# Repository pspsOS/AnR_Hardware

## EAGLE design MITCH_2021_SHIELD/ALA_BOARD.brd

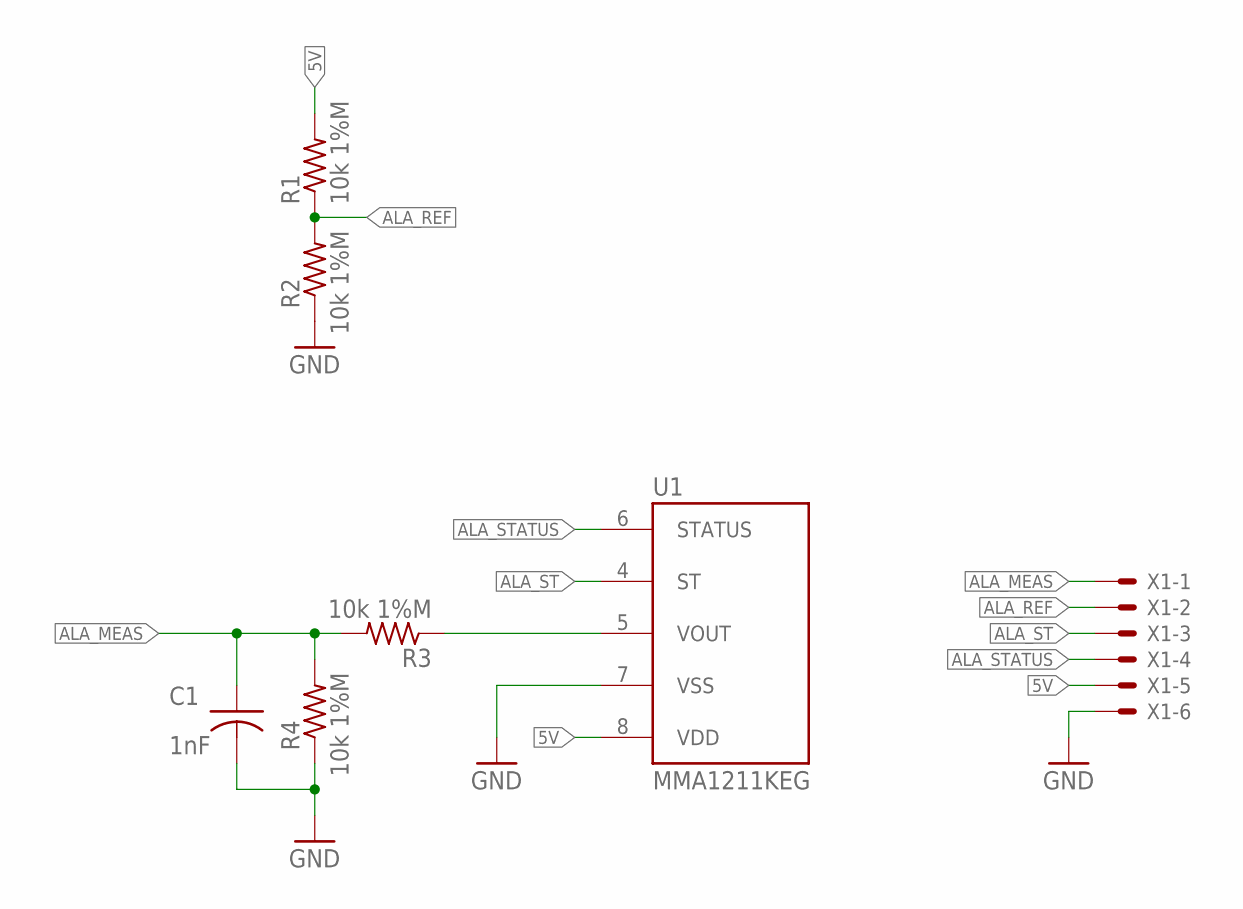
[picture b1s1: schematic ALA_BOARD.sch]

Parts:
C1: 1nF; C0805
R1, R2, R3, R4: 10k 1%M; R0805
U1: MMA1211KEG; SOIC127P1041X355-16N
X1: 22-23-2061

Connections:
5V: R1.2, U1.8 (VDD), X1.5
ALA_MEAS: C1.1, R3.2, R4.2, X1.1
ALA_REF: R1.1, R2.2, X1.2
ALA_ST: U1.4 (ST), X1.3
ALA_STATUS: U1.6 (STATUS), X1.4
GND: C1.2, R2.1, R4.1, U1.7 (VSS), X1.6
VOUT: R3.1, U1.5 (VOUT)

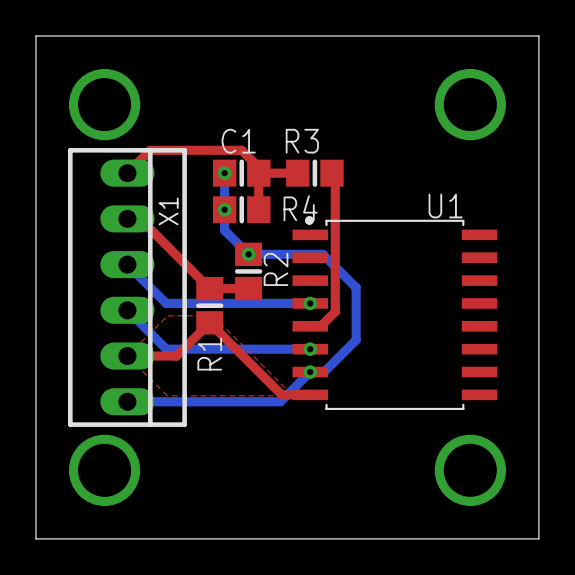
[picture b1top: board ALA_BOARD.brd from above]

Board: 2 copper layers, 27.9 x 27.9 mm, 7 parts (0 on the bottom side), 7 nets.

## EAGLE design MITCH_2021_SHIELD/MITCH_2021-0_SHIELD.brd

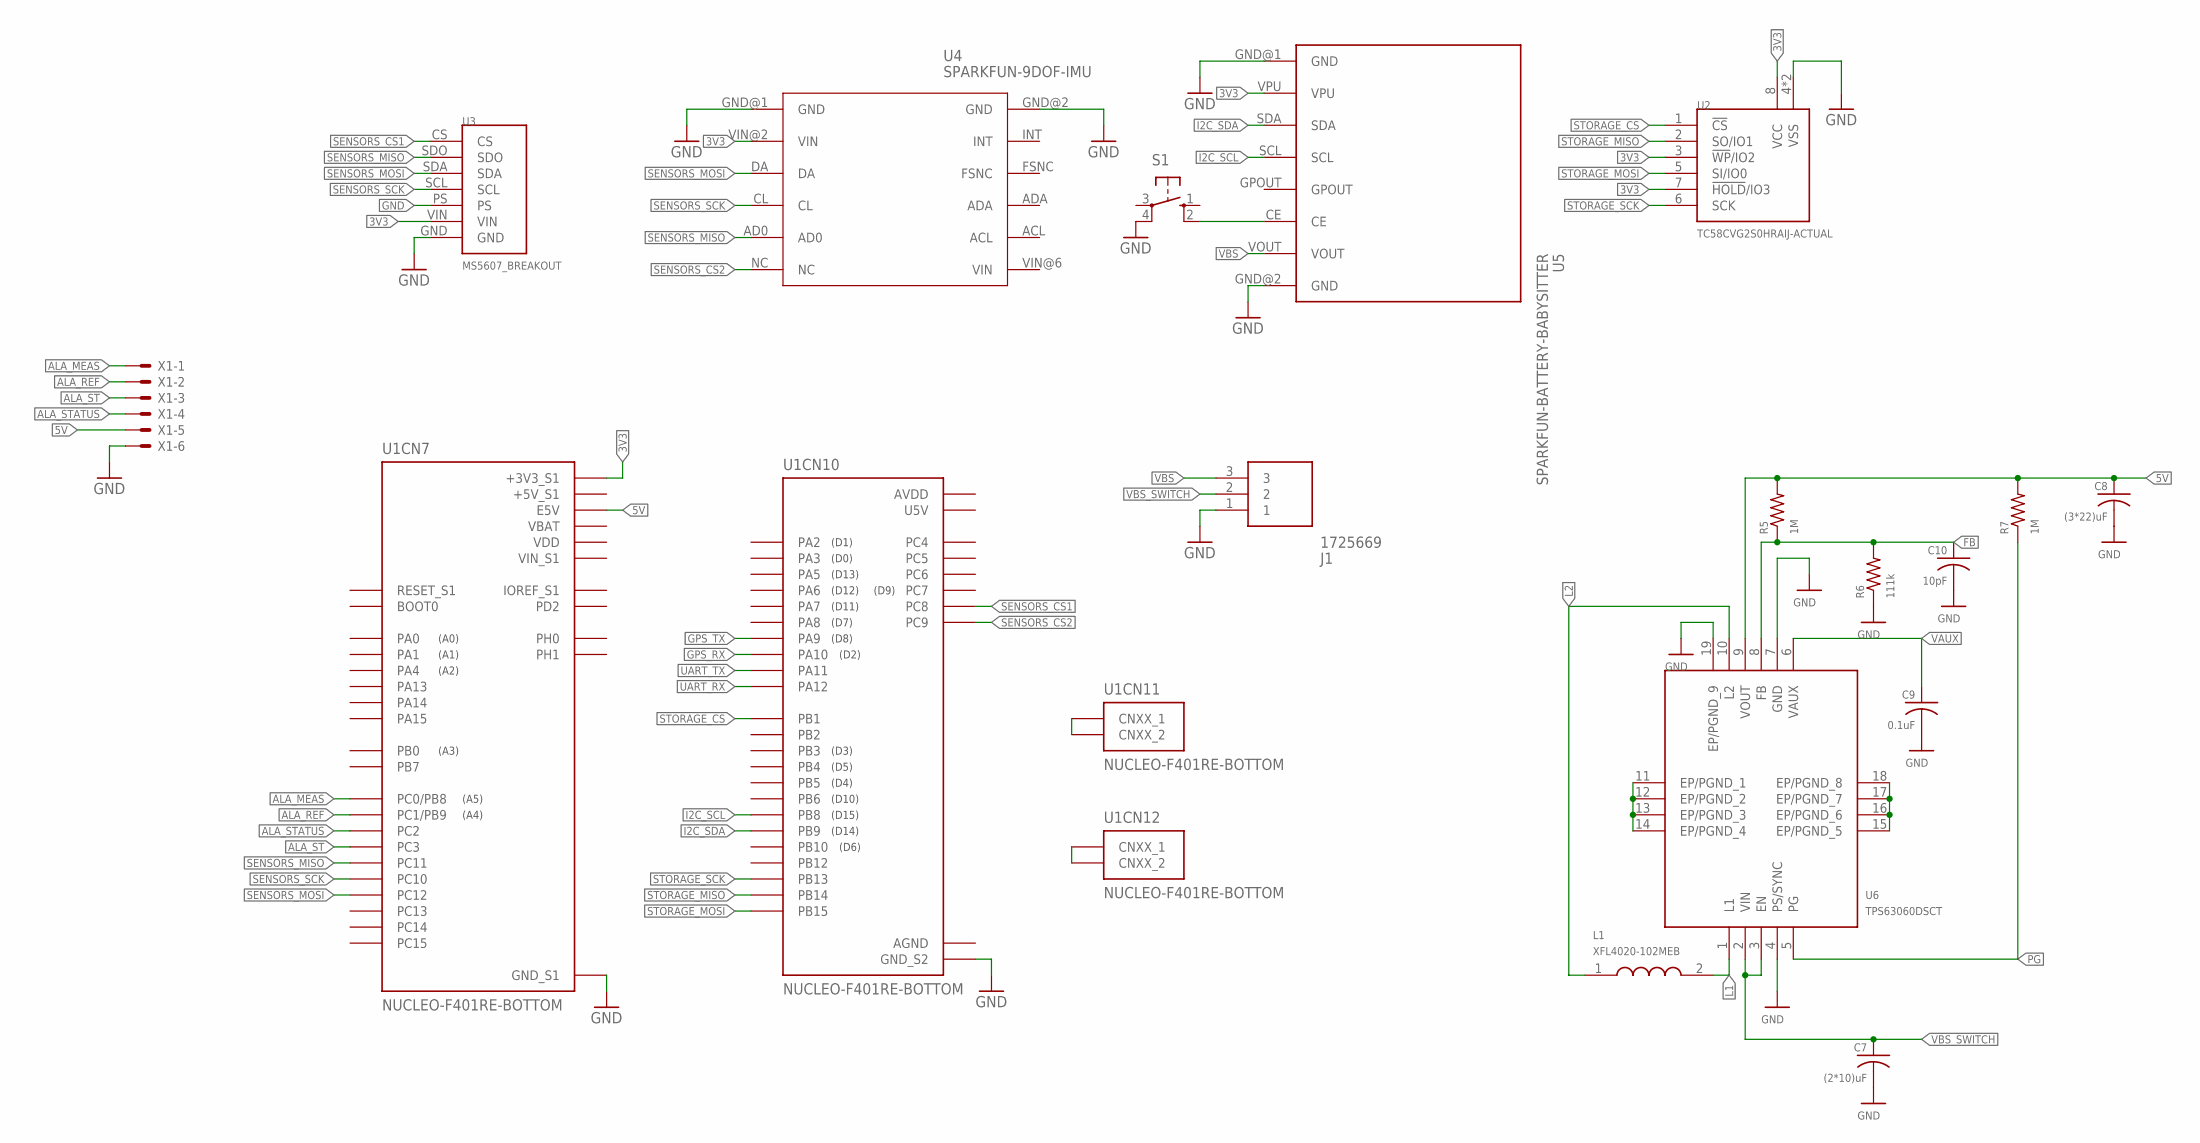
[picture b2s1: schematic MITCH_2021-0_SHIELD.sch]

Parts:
C7: (2*10)uF; C0805
C8: (3*22)uF; C0805
C9: 0.1uF; C0805
C10: 10pF; C0805
J1: 1725669
L1: XFL4020-102MEB; XFL4020102MEB
R5, R7: 1M; R0805
R6: 111k; R0805
S1: 10-XX; B3F-10XX
U1: NUCLEO-F401RE-BOTTOM; ST_NUCLEO-F401RE_BOTTOM
U2: TC58CVG2S0HRAIJ-ACTUAL; COMPUTER2_SON127P800X600X80-9T350X440N
U3: MS5607_BREAKOUT
U4: SPARKFUN-9DOF-IMU; SPARKFUN-9DOF-IMU1
U5: SPARKFUN-BATTERY-BABYSITTER
U6: TPS63060DSCT
X1: 22-23-2061

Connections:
3V3: U1.CN7_16 (+3V3_S1), U2.3 (!WP!/IO2), U2.7 (!HOLD!/IO3), U2.8 (VCC), U3.VIN, U4.VIN@2 (VIN), U5.VPU
5V: C8.1, R5.2, R7.2, U1.CN7_6 (E5V), U6.9 (VOUT), X1.5
+5V_S1: U1.CN7_18 (+5V_S1)
AGND: U1.CN10_32 (AGND)
ALA_MEAS: U1.CN7_38 (PC0/PB8), X1.1
ALA_REF: U1.CN7_36 (PC1/PB9), X1.2
ALA_ST: U1.CN7_37 (PC3), X1.3
ALA_STATUS: U1.CN7_35 (PC2), X1.4
AVDD: U1.CN10_7 (AVDD)
FB: C10.1, R5.1, R6.2, U6.8 (FB)
GND: C7.2, C8.2, C9.2, C10.2, J1.1, R6.1, S1.4 (P1), U1.CN7_8 (GND_S1), U1.CN7_19 (GND_S1), U1.CN7_20 (GND_S1), U1.CN7_22 (GND_S1), U1.CN10_9 (GND_S2), U1.CN10_20 (GND_S2), U2.4 (VSS), U2.9 (VSS), U3.GND, U3.PS, U4.GND@1 (GND), U4.GND@2 (GND), U5.GND@1 (GND), U5.GND@2 (GND), U6.4 (PS/SYNC), U6.7 (GND), U6.11 (EP/PGND_1), U6.12 (EP/PGND_2), U6.13 (EP/PGND_3), U6.14 (EP/PGND_4), U6.15 (EP/PGND_5), U6.16 (EP/PGND_6), U6.17 (EP/PGND_7), U6.18 (EP/PGND_8), U6.19 (EP/PGND_9), X1.6
GPS_RX: U1.CN10_33 (PA10)
GPS_TX: U1.CN10_21 (PA9)
I2C_SCL: U1.CN10_3 (PB8), U5.SCL
I2C_SDA: U1.CN10_5 (PB9), U5.SDA
L1: L1.2, U6.1 (L1)
L2: L1.1, U6.10 (L2)
unnamed: U1.CN12_1 (CNXX_1), U1.CN12_2 (CNXX_2)
unnamed: U1.CN11_1 (CNXX_1), U1.CN11_2 (CNXX_2)
unnamed: S1.2 (S1), U5.CE
PG: R7.1, U6.5 (PG)
SENSORS_CS1: U1.CN10_2 (PC8), U3.CS
SENSORS_CS2: U1.CN10_1 (PC9), U4.NC
SENSORS_MISO: U1.CN7_2 (PC11), U3.SDO, U4.AD0
SENSORS_MOSI: U1.CN7_3 (PC12), U3.SDA, U4.DA
SENSORS_SCK: U1.CN7_1 (PC10), U3.SCL, U4.CL
STORAGE_CS: U1.CN10_24 (PB1), U2.1 (!CS!)
STORAGE_MISO: U1.CN10_28 (PB14), U2.2 (SO/IO1)
STORAGE_MOSI: U1.CN10_26 (PB15), U2.5 (SI/IO0)
STORAGE_SCK: U1.CN10_30 (PB13), U2.6 (SCK)
U5V: U1.CN10_8 (U5V)
UART_RX: U1.CN10_12 (PA12)
UART_TX: U1.CN10_14 (PA11)
VAUX: C9.1, U6.6 (VAUX)
VBAT: U1.CN7_33 (VBAT)
VBS: J1.3, U5.VOUT
VBS_SWITCH: C7.1, J1.2, U6.2 (VIN), U6.3 (EN)
VDD: U1.CN7_5 (VDD)
VIN_S1: U1.CN7_24 (VIN_S1)

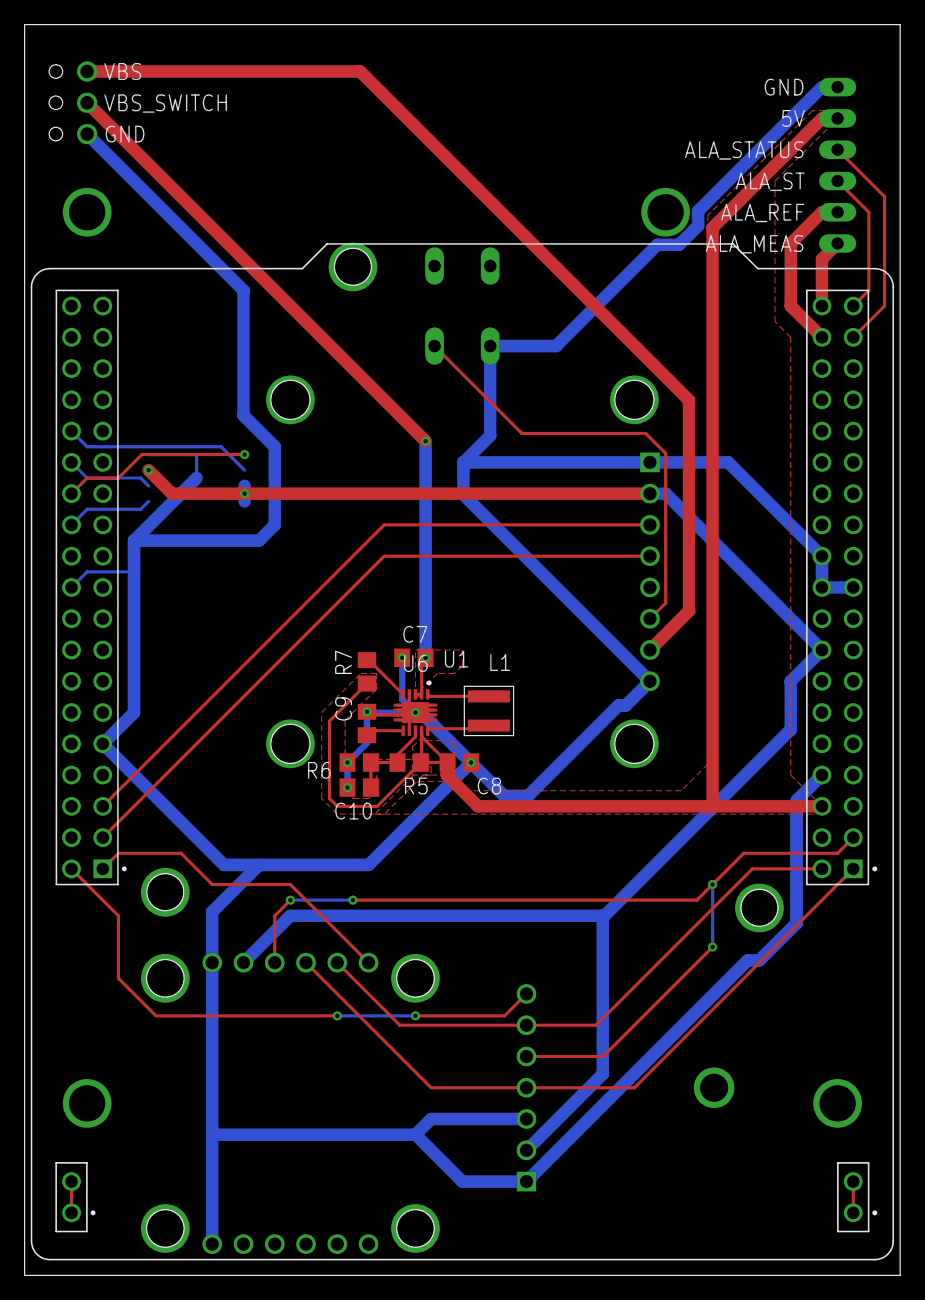
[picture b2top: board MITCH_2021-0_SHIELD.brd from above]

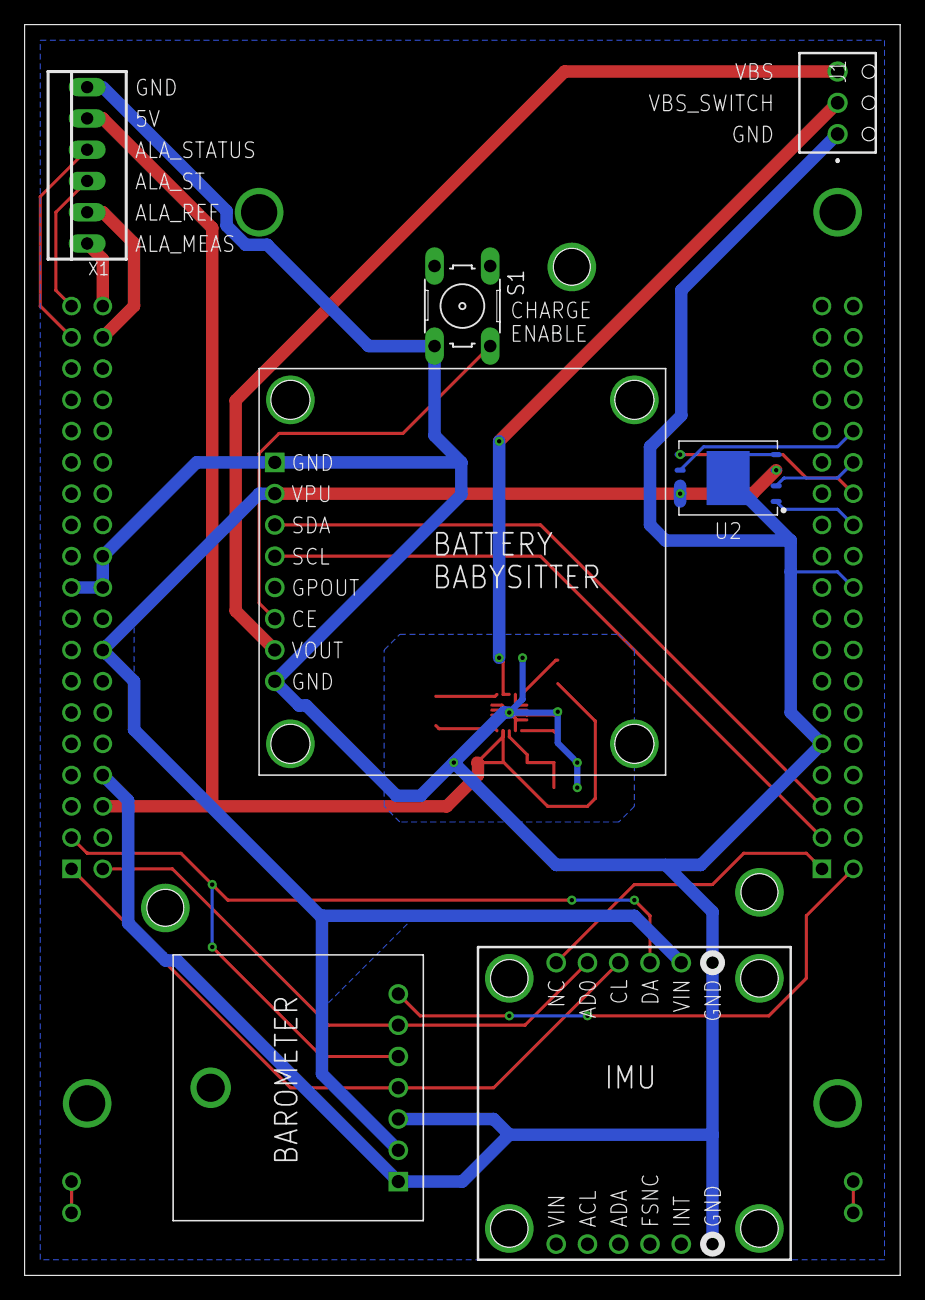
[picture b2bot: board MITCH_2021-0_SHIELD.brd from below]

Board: 2 copper layers, 71.1 x 101.6 mm, 17 parts (7 on the bottom side), 28 nets.

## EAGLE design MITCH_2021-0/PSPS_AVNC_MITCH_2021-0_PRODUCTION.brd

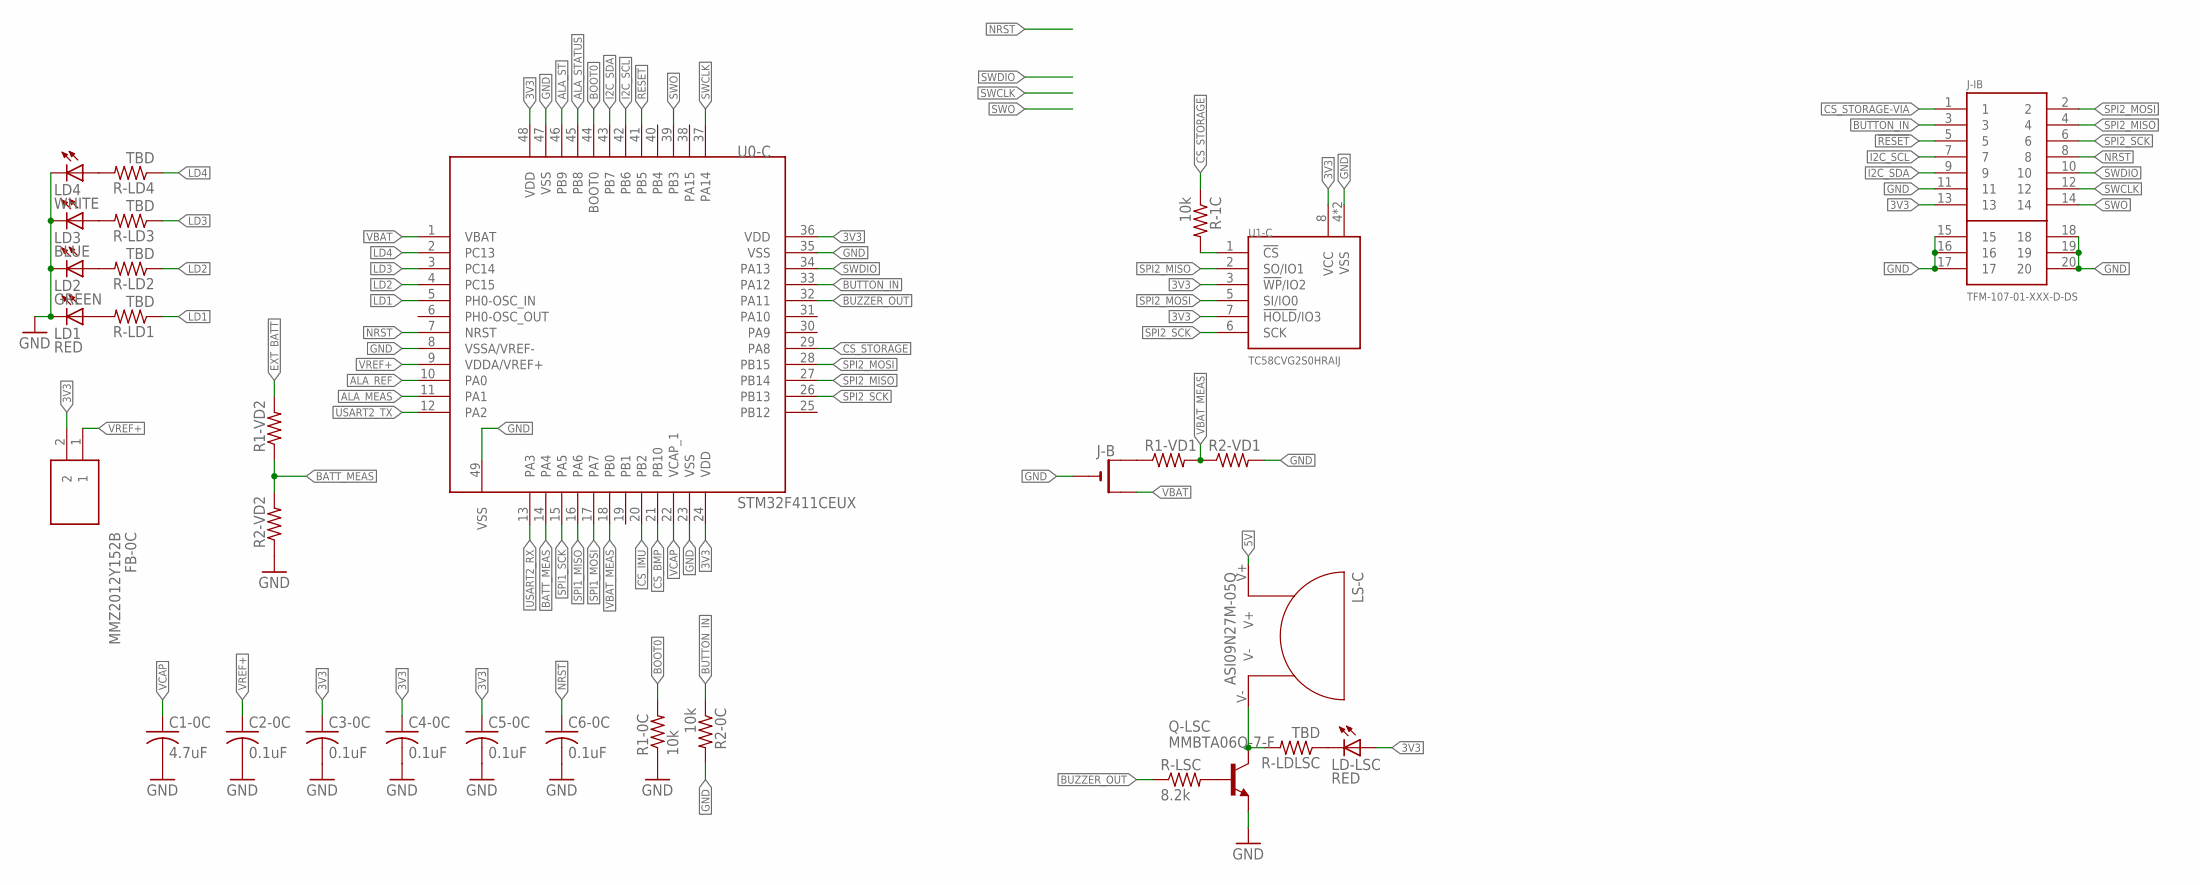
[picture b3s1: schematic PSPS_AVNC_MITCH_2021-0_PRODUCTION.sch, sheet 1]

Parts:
C1-0C: 4.7uF; C0805
C2-0C, C3-0C, C4-0C, C5-0C, C6-0C: 0.1uF; C0805
FB-0C: MMZ2012Y152B; BEADC2012X105N
J-B: CR1220SMT; CR1220-SMD
J-IB: TFM-107-01-XXX-D-DS
LD1: RED; CHIPLED_0805
LD2: GREEN; CHIPLED_0805
LD3: BLUE; CHIPLED_0805
LD4: WHITE; CHIPLED_0805
LD-LSC: RED; CHIPLED_0805
LS-C: ASI09N27M-05Q
Q-LSC: MMBTA06Q-7-F; SOT23
R1-0C, R2-0C: 10k; R0805
R1-VD1, R1-VD2, R2-VD1, R2-VD2: R-US_R0805; R0805
R-1C: 10k; R0805
R-LD1, R-LD2, R-LD3, R-LD4: TBD; R0805
R-LDLSC: TBD; R0805
R-LSC: 8.2k; R0805
U0-C: STM32F411CEUX; QFN50P700X700X50-49T560N
U1-C: TC58CVG2S0HRAIJ; SON127P800X600X80-9T350X440N

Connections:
3V3: C3-0C.1, C4-0C.1, C5-0C.1, FB-0C.2, J-IB.13, LD-LSC.A, U0-C.24 (VDD), U0-C.36 (VDD), U0-C.48 (VDD), U1-C.3 (!WP!/IO2), U1-C.7 (!HOLD!/IO3), U1-C.8 (VCC); also elsewhere on the board
5V: LS-C.V+; also elsewhere on the board
!RESET!: J-IB.5, U0-C.41 (PB5)
ALA_MEAS: U0-C.11 (PA1); also elsewhere on the board
ALA_REF: U0-C.10 (PA0); also elsewhere on the board
ALA_ST: U0-C.46 (PB9); also elsewhere on the board
ALA_STATUS: U0-C.45 (PB8); also elsewhere on the board
BATT_MEAS: R1-VD2.1, R2-VD2.2, U0-C.14 (PA4)
BOOT0: R1-0C.2, U0-C.44 (BOOT0)
BUTTON_IN: J-IB.3, R2-0C.1, U0-C.33 (PA12)
BUZZER_OUT: R-LSC.1, U0-C.32 (PA11)
CS_BMP: U0-C.21 (PB10); also elsewhere on the board
CS_IMU: U0-C.20 (PB2); also elsewhere on the board
CS_STORAGE: R-1C.1, U0-C.29 (PA8)
CS_STORAGE-VIA: J-IB.1, R-1C.2, U1-C.1 (!CS!)
EXT_BATT: R1-VD2.2
GND: C1-0C.2, C2-0C.2, C3-0C.2, C4-0C.2, C5-0C.2, C6-0C.2, J-B.-, J-IB.11, J-IB.15, J-IB.16, J-IB.17, J-IB.18, J-IB.19, J-IB.20, LD1.C, LD2.C, LD3.C, LD4.C, Q-LSC.3 (E), R1-0C.1, R2-0C.2, R2-VD1.2, R2-VD2.1, U0-C.8 (VSSA/VREF-), U0-C.23 (VSS), U0-C.35 (VSS), U0-C.47 (VSS), U0-C.49 (VSS), U1-C.4 (VSS), U1-C.9 (VSS); also elsewhere on the board
I2C_SCL: J-IB.7, U0-C.42 (PB6)
I2C_SDA: J-IB.9, U0-C.43 (PB7)
LD1: R-LD1.1, U0-C.5 (PH0-OSC_IN)
LD2: R-LD2.1, U0-C.4 (PC15)
LD3: R-LD3.1, U0-C.3 (PC14)
LD4: R-LD4.1, U0-C.2 (PC13)
unnamed: Q-LSC.1 (B), R-LSC.2
unnamed: LD1.A, R-LD1.2
unnamed: LD2.A, R-LD2.2
unnamed: LD3.A, R-LD3.2
unnamed: LD4.A, R-LD4.2
unnamed: J-B.+$1 (+), R1-VD1.1
unnamed: LS-C.V-, Q-LSC.2 (C), R-LDLSC.2
unnamed: LD-LSC.C, R-LDLSC.1
NRST: C6-0C.1, J-IB.8, U0-C.7 (NRST)
SPI1_MISO: U0-C.16 (PA6); also elsewhere on the board
SPI1_MOSI: U0-C.17 (PA7); also elsewhere on the board
SPI1_SCK: U0-C.15 (PA5); also elsewhere on the board
SPI2_MISO: J-IB.4, U0-C.27 (PB14), U1-C.2 (SO/IO1)
SPI2_MOSI: J-IB.2, U0-C.28 (PB15), U1-C.5 (SI/IO0)
SPI2_SCK: J-IB.6, U0-C.26 (PB13), U1-C.6 (SCK)
SWCLK: J-IB.12, U0-C.37 (PA14)
SWDIO: J-IB.10, U0-C.34 (PA13)
SWO: J-IB.14, U0-C.39 (PB3)
USART2_RX: U0-C.13 (PA3); also elsewhere on the board
USART2_TX: U0-C.12 (PA2); also elsewhere on the board
VBAT: J-B.+$2 (+1), U0-C.1 (VBAT); also elsewhere on the board
VBAT_MEAS: R1-VD1.2, R2-VD1.1, U0-C.18 (PB0)
VCAP: C1-0C.1, U0-C.22 (VCAP_1)
VREF+: C2-0C.1, FB-0C.1, U0-C.9 (VDDA/VREF+)

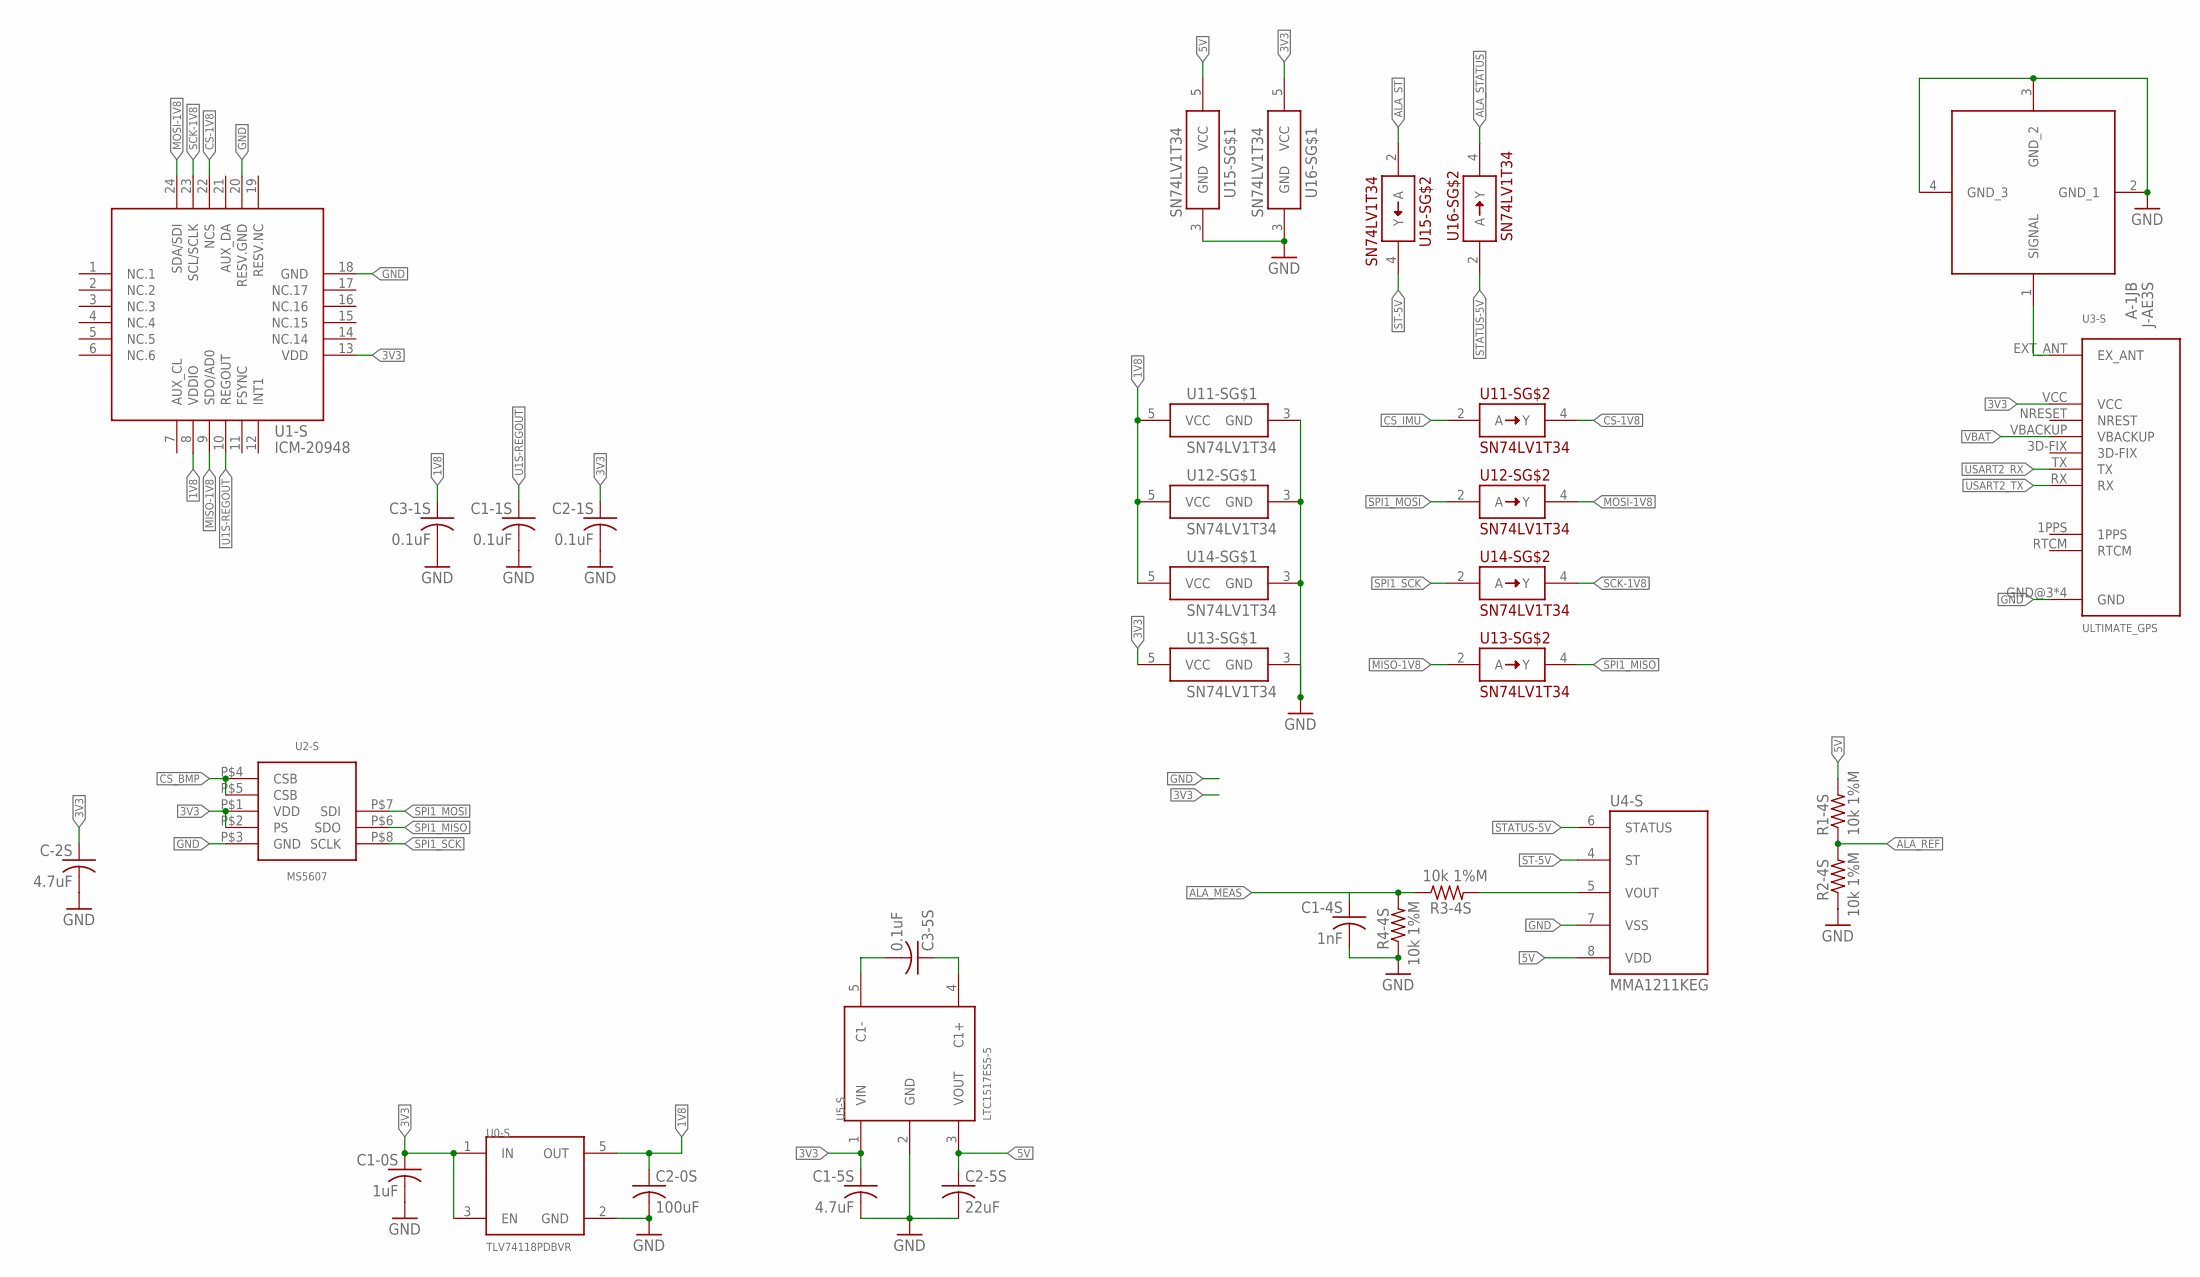
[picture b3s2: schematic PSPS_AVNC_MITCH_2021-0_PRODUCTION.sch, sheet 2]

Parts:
C1-0S: 1uF; C0805
C1-1S, C2-1S, C3-1S, C3-5S: 0.1uF; C0805
C1-4S: 1nF; C0805
C1-5S: 4.7uF; C0805
C2-0S: 100uF; C0805
C2-5S: 22uF; C0805
C-2S: 4.7uF; C0805
J-AE3S: A-1JB; A1JB
R1-4S, R2-4S, R3-4S, R4-4S: 10k 1%M; R0805
U0-S: TLV74118PDBVR; SOT95P280X145-5N
U1-S: ICM-20948; QFN40P300X300X105-25T159X175
U2-S: MS5607
U3-S: ULTIMATE_GPS; FGPMMOPA6H
U4-S: MMA1211KEG; SOIC127P1041X355-16N
U5-S: LTC1517ES5-5; SOT95P280X145-5N
U11-S, U12-S, U13-S, U14-S, U15-S, U16-S: SN74LV1T34; SOT65P210X110-5

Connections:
1V8: C2-0S.1, C3-1S.1, U0-S.5 (OUT), U1-S.8 (VDDIO), U11-S.5 (VCC), U12-S.5 (VCC), U14-S.5 (VCC)
3V3: C1-0S.1, C1-5S.1, C2-1S.1, C-2S.1, U0-S.1 (IN), U0-S.3 (EN), U1-S.13 (VDD), U2-S.P$1 (VDD), U2-S.P$2 (PS), U3-S.VCC, U5-S.1 (VIN), U13-S.5 (VCC), U16-S.5 (VCC); also elsewhere on the board
5V: C2-5S.1, R1-4S.2, U4-S.8 (VDD), U5-S.3 (VOUT), U15-S.5 (VCC); also elsewhere on the board
ALA_MEAS: C1-4S.1, R3-4S.1, R4-4S.2; also elsewhere on the board
ALA_REF: R1-4S.1, R2-4S.2; also elsewhere on the board
ALA_ST: U15-S.2 (A); also elsewhere on the board
ALA_STATUS: U16-S.4 (Y); also elsewhere on the board
CS-1V8: U1-S.22 (NCS), U11-S.4 (Y)
CS_BMP: U2-S.P$4 (CSB), U2-S.P$5 (CSB); also elsewhere on the board
CS_IMU: U11-S.2 (A); also elsewhere on the board
GND: C1-0S.2, C1-1S.2, C1-4S.2, C1-5S.2, C2-0S.2, C2-1S.2, C2-5S.2, C3-1S.2, C-2S.2, J-AE3S.2 (GND_1), J-AE3S.3 (GND_2), J-AE3S.4 (GND_3), R2-4S.1, R4-4S.1, U0-S.2 (GND), U1-S.18 (GND), U1-S.20 (RESV.GND), U2-S.P$3 (GND), U3-S.GND@3 (GND), U3-S.GND@8 (GND), U3-S.GND@12 (GND), U3-S.GND@19 (GND), U4-S.7 (VSS), U5-S.2 (GND), U11-S.3 (GND), U12-S.3 (GND), U13-S.3 (GND), U14-S.3 (GND), U15-S.3 (GND), U16-S.3 (GND); also elsewhere on the board
MISO-1V8: U1-S.9 (SDO/AD0), U13-S.2 (A)
MOSI-1V8: U1-S.24 (SDA/SDI), U12-S.4 (Y)
unnamed: C3-5S.1, U5-S.4 (C1+)
unnamed: C3-5S.2, U5-S.5 (C1-)
unnamed: J-AE3S.1 (SIGNAL), U3-S.EXT_ANT (EX_ANT)
unnamed: R3-4S.2, U4-S.5 (VOUT)
SCK-1V8: U1-S.23 (SCL/SCLK), U14-S.4 (Y)
SPI1_MISO: U2-S.P$6 (SDO), U13-S.4 (Y); also elsewhere on the board
SPI1_MOSI: U2-S.P$7 (SDI), U12-S.2 (A); also elsewhere on the board
SPI1_SCK: U2-S.P$8 (SCLK), U14-S.2 (A); also elsewhere on the board
ST-5V: U4-S.4 (ST), U15-S.4 (Y)
STATUS-5V: U4-S.6 (STATUS), U16-S.2 (A)
U1S-REGOUT: C1-1S.1, U1-S.10 (REGOUT)
USART2_RX: U3-S.TX; also elsewhere on the board
USART2_TX: U3-S.RX; also elsewhere on the board
VBAT: U3-S.VBACKUP; also elsewhere on the board

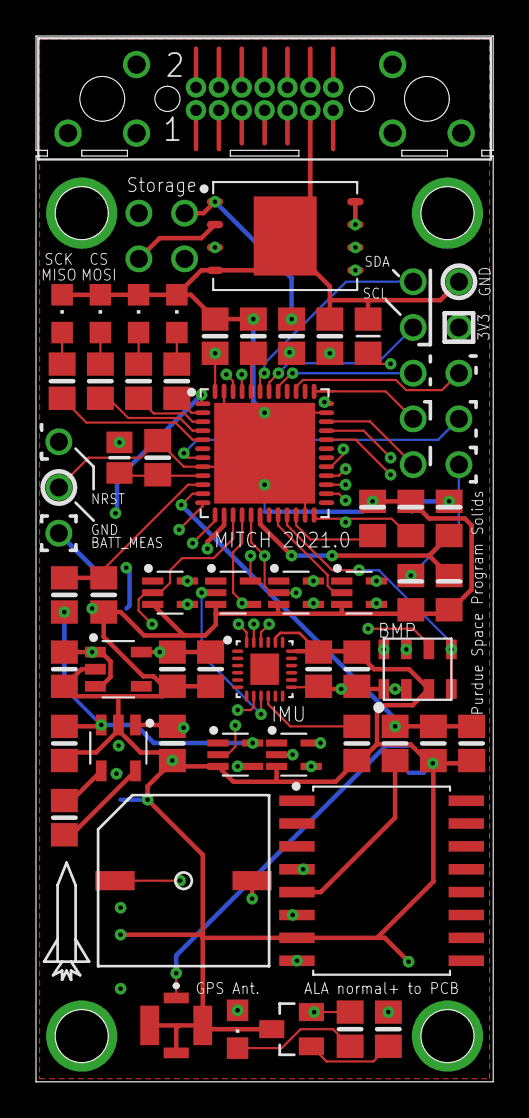
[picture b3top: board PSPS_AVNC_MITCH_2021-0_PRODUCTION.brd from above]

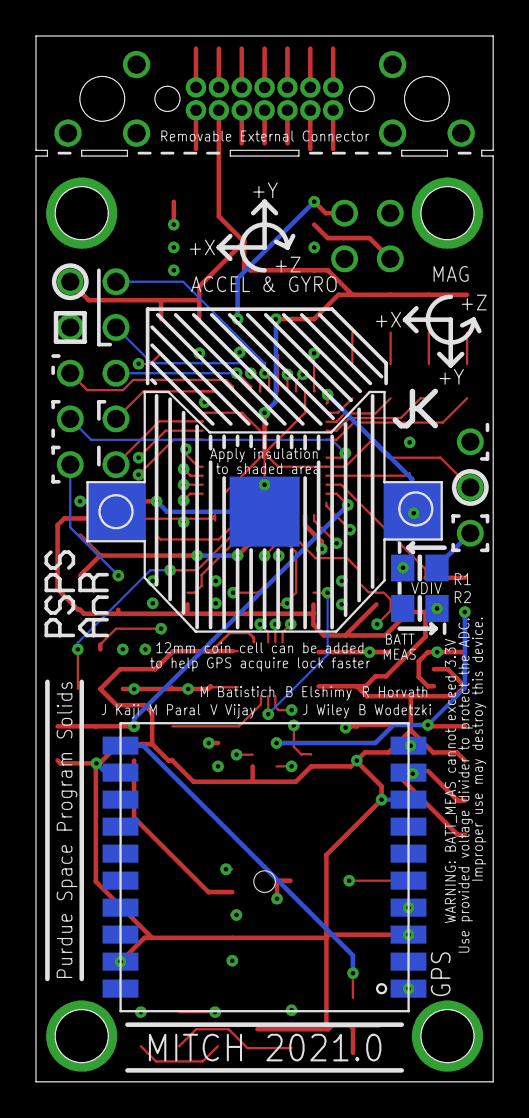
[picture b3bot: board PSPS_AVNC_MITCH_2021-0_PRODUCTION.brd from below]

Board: 4 copper layers, 25.4 x 58.1 mm, 58 parts (4 on the bottom side), 58 nets.

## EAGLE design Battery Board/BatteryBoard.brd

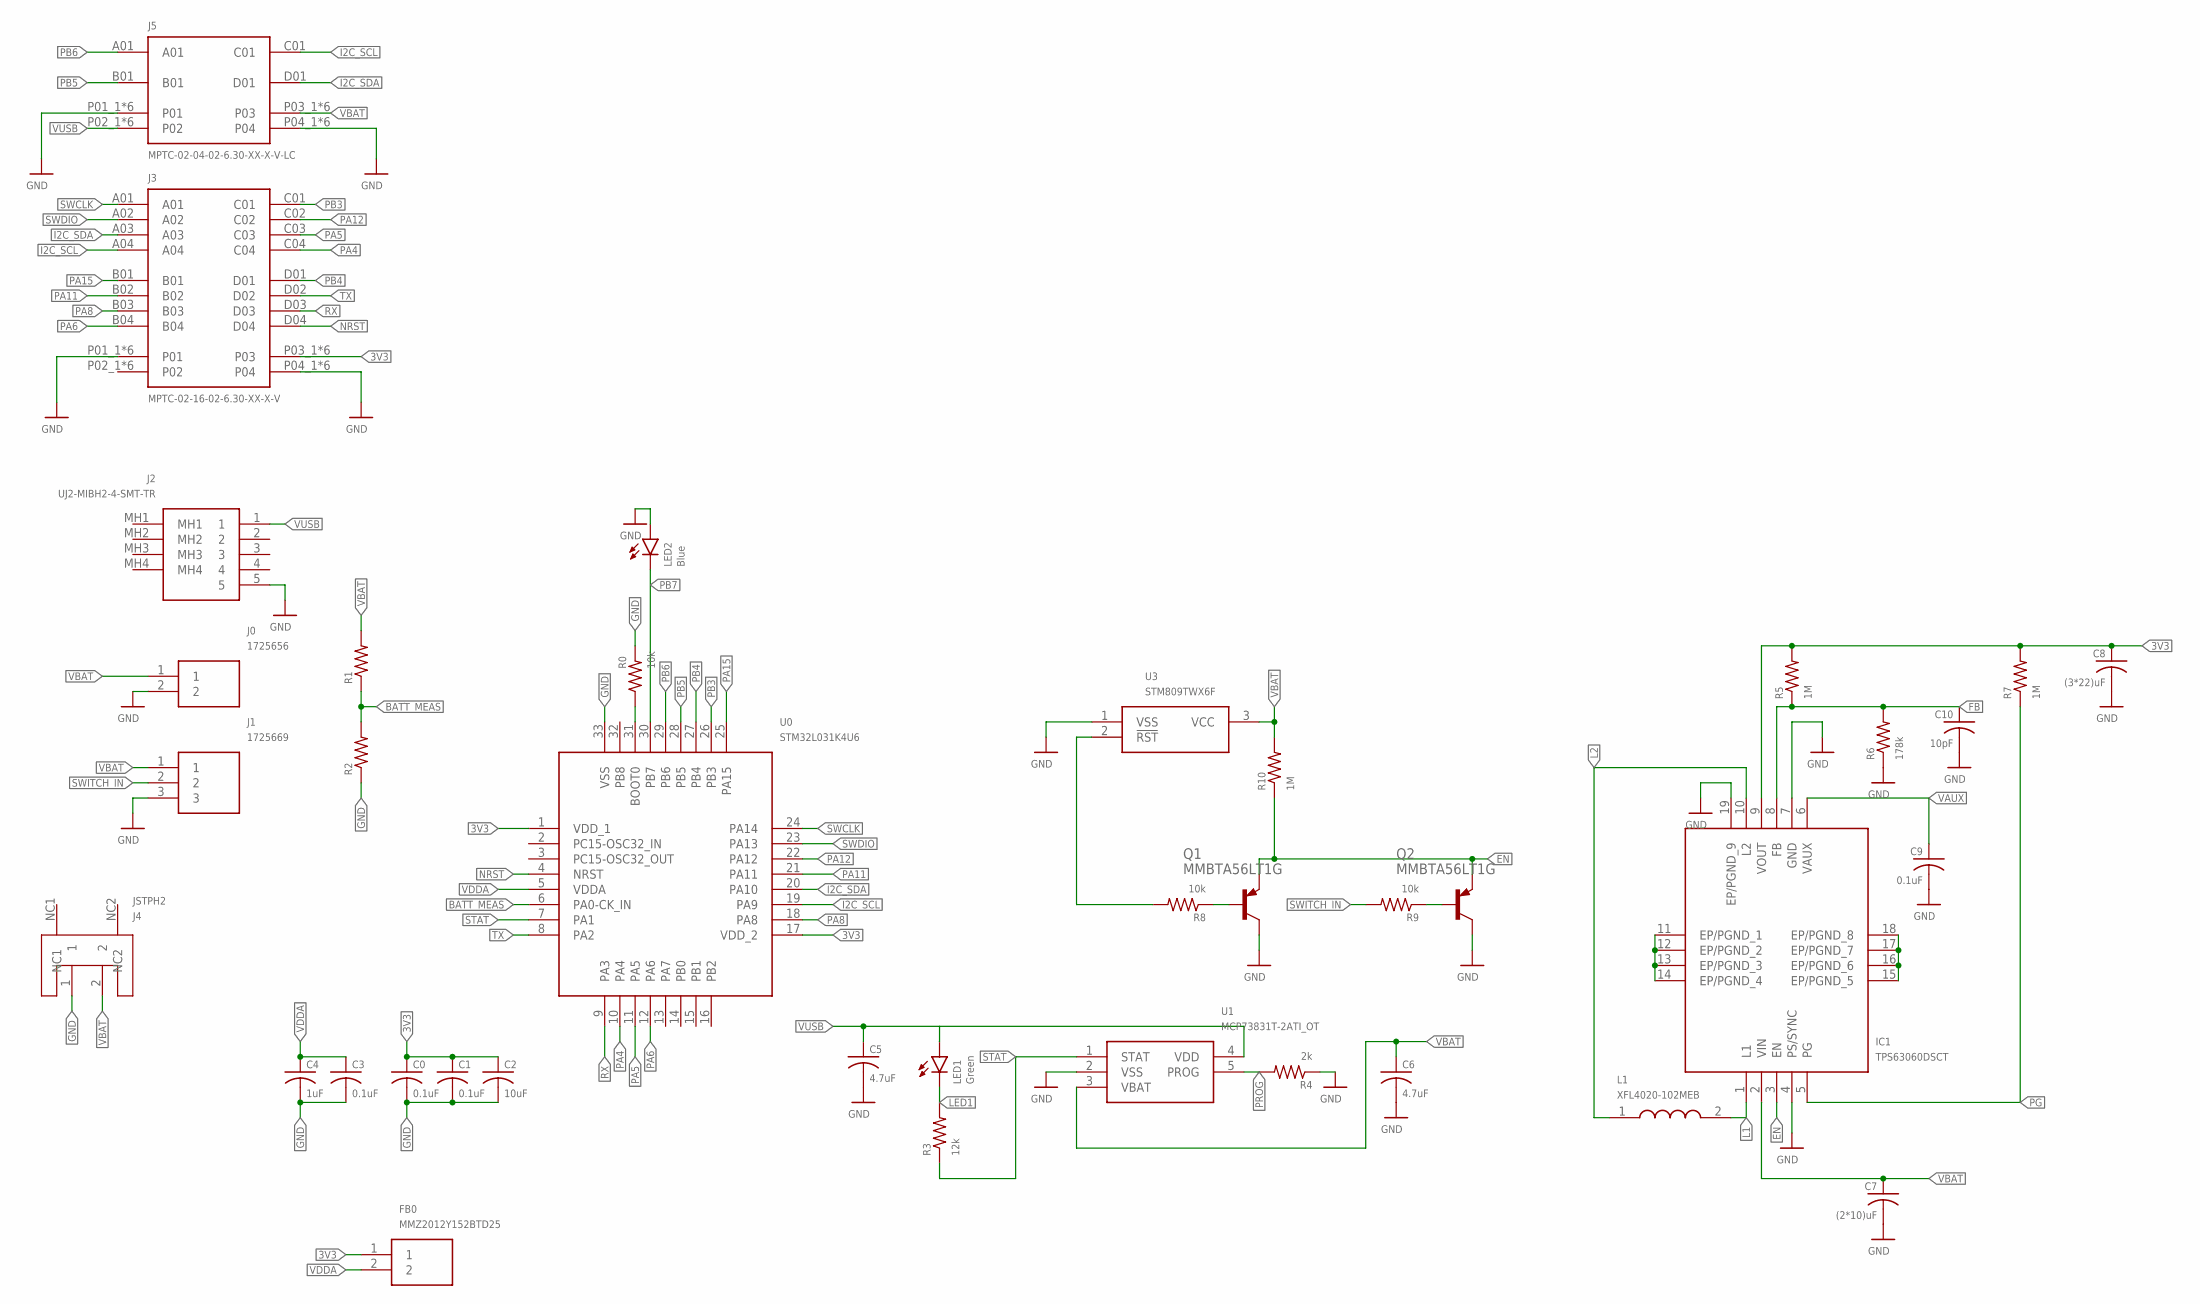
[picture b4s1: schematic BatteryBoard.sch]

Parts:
C0, C1, C3, C9: 0.1uF; C0805
C2: 10uF; C0805
C4: 1uF; C0805
C5, C6: 4.7uF; C0805
C7: (2*10)uF; C0805
C8: (3*22)uF; C0805
C10: 10pF; C0805
FB0: MMZ2012Y152BTD25; BEADC2012X105N
IC1: TPS63060DSCT
J0: 1725656
J1: 1725669
J2: UJ2-MIBH2-4-SMT-TR; UJ2MIBH24SMTTR
J3: MPTC-02-16-02-6.30-XX-X-V; SAMTEC_MPTC-02-16-02-6.30-XX-X-V
J4: JSTPH2
J5: MPTC-02-04-02-6.30-XX-X-V-LC; SAMTEC_MPTC-02-04-02-6.30-XX-X-V-LC
L1: XFL4020-102MEB; XFL4020102MEB
LED1: Green; CHIP-LED0805
LED2: Blue; CHIP-LED0805
Q1, Q2: MMBTA56LT1G; SOT23-BEC
R0, R8, R9: 10k; R0805
R1, R2: R-US_R0805; R0805
R3: 12k; R0805
R4: 2k; R0805
R5, R7, R10: 1M; R0805
R6: 178k; R0805
U0: STM32L031K4U6; QFN50P500X500X60-33N
U1: MCP73831T-2ATI_OT; SOT95P270X145-5N
U3: STM809TWX6F; SOT103P237X112-3N

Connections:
3V3: C0.1, C1.1, C2.1, C8.1, FB0.1, IC1.9 (VOUT), J3.P03_1 (P03), J3.P03_2 (P03), J3.P03_3 (P03), J3.P03_4 (P03), J3.P03_5 (P03), J3.P03_6 (P03), R5.2, R7.2, U0.1 (VDD_1), U0.17 (VDD_2)
BATT_MEAS: R1.1, R2.2, U0.6 (PA0-CK_IN)
BOOT0: R0.1, U0.31 (BOOT0)
EN: IC1.3 (EN), Q1.E, Q2.E, R10.1
FB: C10.1, IC1.8 (FB), R5.1, R6.2
GND: C0.2, C1.2, C2.2, C3.2, C4.2, C5.2, C6.2, C7.2, C8.2, C9.2, C10.2, IC1.4 (PS/SYNC), IC1.7 (GND), IC1.11 (EP/PGND_1), IC1.12 (EP/PGND_2), IC1.13 (EP/PGND_3), IC1.14 (EP/PGND_4), IC1.15 (EP/PGND_5), IC1.16 (EP/PGND_6), IC1.17 (EP/PGND_7), IC1.18 (EP/PGND_8), IC1.19 (EP/PGND_9), J0.2, J1.3, J2.5, J3.P01_1 (P01), J3.P01_2 (P01), J3.P01_3 (P01), J3.P01_4 (P01), J3.P01_5 (P01), J3.P01_6 (P01), J3.P04_1 (P04), J3.P04_2 (P04), J3.P04_3 (P04), J3.P04_4 (P04), J3.P04_5 (P04), J3.P04_6 (P04), J4.1, J5.P01_1 (P01), J5.P01_2 (P01), J5.P01_3 (P01), J5.P01_4 (P01), J5.P01_5 (P01), J5.P01_6 (P01), J5.P04_1 (P04), J5.P04_2 (P04), J5.P04_3 (P04), J5.P04_4 (P04), J5.P04_5 (P04), J5.P04_6 (P04), LED2.A, Q1.C, Q2.C, R0.2, R2.1, R4.1, R6.1, U0.33 (VSS), U1.2 (VSS), U3.1 (VSS)
I2C_SCL: J3.A04, J5.C01, U0.19 (PA9)
I2C_SDA: J3.A03, J5.D01, U0.20 (PA10)
L1: IC1.1 (L1), L1.2
L2: IC1.10 (L2), L1.1
LED1: LED1.C, R3.2
unnamed: Q1.B, R8.1
unnamed: Q2.B, R9.1
NRST: J3.D04, U0.4 (NRST)
P02: J3.P02_1 (P02), J3.P02_2 (P02), J3.P02_3 (P02), J3.P02_4 (P02), J3.P02_5 (P02), J3.P02_6 (P02)
PA4: J3.C04, U0.10 (PA4)
PA5: J3.C03, U0.11 (PA5)
PA6: J3.B04, U0.12 (PA6)
PA8: J3.B03, U0.18 (PA8)
PA11: J3.B02, U0.21 (PA11)
PA12: J3.C02, U0.22 (PA12)
PA15: J3.B01, U0.25 (PA15)
PB3: J3.C01, U0.26 (PB3)
PB4: J3.D01, U0.27 (PB4)
PB5: J5.B01, U0.28 (PB5)
PB6: J5.A01, U0.29 (PB6)
PB7: LED2.C, U0.30 (PB7)
PG: IC1.5 (PG), R7.1
PROG: R4.2, U1.5 (PROG)
PROTECTION_NRST: R8.2, U3.2 (!RST)
RX: J3.D03, U0.9 (PA3)
STAT: R3.1, U0.7 (PA1), U1.1 (STAT)
SWCLK: J3.A01, U0.24 (PA14)
SWDIO: J3.A02, U0.23 (PA13)
SWITCH_IN: J1.2, R9.2
TX: J3.D02, U0.8 (PA2)
VAUX: C9.1, IC1.6 (VAUX)
VBAT: C6.1, C7.1, IC1.2 (VIN), J0.1, J1.1, J4.2, J5.P03_1 (P03), J5.P03_2 (P03), J5.P03_3 (P03), J5.P03_4 (P03), J5.P03_5 (P03), J5.P03_6 (P03), R1.2, R10.2, U1.3 (VBAT), U3.3 (VCC)
VDDA: C3.1, C4.1, FB0.2, U0.5 (VDDA)
VUSB: C5.1, J2.1, J5.P02_1 (P02), J5.P02_2 (P02), J5.P02_3 (P02), J5.P02_4 (P02), J5.P02_5 (P02), J5.P02_6 (P02), LED1.A, U1.4 (VDD)
